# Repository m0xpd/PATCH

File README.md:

# PATCH
PATCH is a simple modular patchbay project for Eurorack.

PATCH started with an application to develop a simple interface to my [UMC1820 Audio Interface](https://www.behringer.com/product.html?modelCode=0805-AAN) and my [FX2000 Effects Processor](https://www.behringer.com/product.html?modelCode=P0A3P), both of which have rear-mounted audio I/O and require some input attentuators to allow them to work as I wish in my system. A patchbay is the perfect way to impose order on the tangle of wires, to avoid searching on the back of cases (especially if they're stacked or racked) and is also the logical place to implement attenuating pads, where required. 

The image below shows two PATCH patchbay modules (inside the yellow rounded rectangle) implementing the complete interface to the UMC1820 and FX2000

Note that the UMC1820 [does not need attenuators to handle modular signals directly](https://modwiggler.com/forum/viewtopic.php?p=2936306#p2936306). Indeed, it is specified to be capable of handling inputs up to +18dBu. However, this requires that the inputs are set to LINE (obviously), that the PADs are applied, and the GAIN controls are set way down near the bottom of their travel. I have been pleased to discover that in addition to service as front end of a DAW (or similar application), the UMC1820 also operates usefuly as a stand-alone mixer, with 8 channels going in and direct output to the system monitors. In this role, some external attenuation on the inputs is helpful, as it allows the GAIN controls to operate as Level 'faders' over a wider range, with more useful resolution. On the other hand, the FX2000 is specified only to handle inputs up to +4dBu and my modular was easily able to overload its inputs; an external attenuator is certainly required in this case. 

The basic PATCH configuration which services this motivating application, seen in the photos above, is realised by three components: a [front panel](https://github.com/m0xpd/PATCH/tree/main/Hardware/Front%20Panel#readme), a [socket board](https://github.com/m0xpd/PATCH/tree/main/Hardware/Socket%20Board#readme), and a [passive board](https://github.com/m0xpd/PATCH/tree/main/Hardware/Passive%20Board#readme). 

The passive board includes pi networks between the 3.5mm jack sockets at input and output of each channel and provides options to normal the 'tip switches' on the jacks to ground if the channel is configured as an input. This tip normalisation is achieved using 1206 surface mount (0 Ohm) resistors (as I figure not many people will bother to use them), whilst the rest of the board uses through-hole components. Partially populating the resistors of the pi network gives the option to set up a potential divider to drop the signal level in either direction, or to set a unity gain 'straight wire' connection. The system shown above has a 24dB pad on the top two channels and two send/return loops implemented on the next four sockets, with 12dB pads on the sends and straight-wire returns.

Populating the pads is up to you - I'm using a 15k / 1k potential divider for the -24dB and 3k3 / 1k1 potential divider for the -12dB. HOWEVER, you should remember that the device you're plugging into has finite (and possibly LOW) input impedance, which will sit in parallel with the botttom resistor of the potential divider, so either don't take the open-circuit calculations too seriously, or account for this loading in your design!

The Passive board, which makes up PATCH's standard patchbay configuration, houses a set of 3.5mm sockets which face to the rear, mirroring those on the front panel. Standard Eurorack patch leads (or other leads made up for custom applications, such as the 3.5 mm to 6.5mm right angle jacks I've made to hook up to the back of my FX2000) connect to these sockets, when the patchbay is used in the modular:

***

The minimum order quantity at [JLC](https://jlcpcb.com/) (typical of all pcb houses) for the front panel and socket board left me with some spare resources after I'd finished my interface to the Behringer "off-board" units, so I also develped a [passive multiple board](https://github.com/m0xpd/PATCH/tree/main/Hardware/Passive%20Multiple%20Board#readme), and a [buffered multiple board](https://github.com/m0xpd/PATCH/tree/main/Hardware/Buffered%20Multiple%20Board#readme) so as not to waste the relatively expensive Aluminium front panels. 

These multiples share the front panel and the socket board with the basic patchbay design, but use a different final board. 

The complete set of PATCH system panels are seen below.

Both the passive multiple and the buffered multiple are organised as two 1 in, 2 out sections, with the input to the second section normalled to the output of the first, such that the multiple can be operated as two 1 -> 2 units or one 1 -> 4 unit.

A PATCH buffered multiple is seen below:

All the system components are described in the [hardware folder](https://github.com/m0xpd/PATCH/tree/main/Hardware#readme), where schematics, PCB layouts and front panel designs are presented as [KiCad](https://www.kicad.org/) projects.

# PATCH Multicore

The PATCH system now (as at 5 June 2024) also has a multicore option, realised by a pair of boards. The multicore functionality was first suggested by "CoogLFish", within the "Issues" section of this repo and whose inspiration is acknowledged.

The boards are offered in two forms. First, the ["low budget"](https://github.com/m0xpd/PATCH/tree/main/Hardware/RJ45%20Board#readme) option uses a single UTP cable to join two modules to make a six channel multicore]. Second, the ["high end" alternative](https://github.com/m0xpd/PATCH/tree/main/Hardware/Twin%20RJ45%20Board#readme) uses two UTP cables to achieve the same goal with the possibility of slightly better crosstalk performance. This "Twin" system will also work with cables with shielded twisted pairs such as CAT8 and offer some performance advantages - but I have not yet formally tested this to determine how big the performance advantage (over either the single cable solution or UTP cables) really is. I use CAT6 cables over 1.5m and have not yet noticed issues.

# Other PATCH System Components

There may be still more additions to the PATCH system in future - I have a couple more ideas, but there are lots of other potential projects competing for attention, so watch this space, but don't hold your breath.

# License

PATCH is published under [CC BY-SA 4.0 license.](https://github.com/m0xpd/PATCH/blob/main/LICENSE.txt)

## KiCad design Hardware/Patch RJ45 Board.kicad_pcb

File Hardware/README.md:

This folder contains design files for components of the PATCH modular Eurorack patchbay system.

There are schematics, PCB layouts and a Front Panel design in [KiCad](https://www.kicad.org/) format.

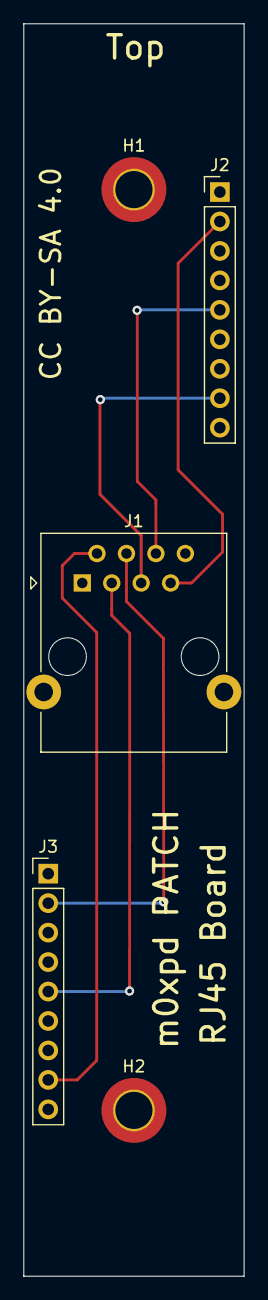
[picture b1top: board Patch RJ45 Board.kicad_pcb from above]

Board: 2 copper layers, 19.0 x 108.0 mm, 5 parts (0 on the bottom side), 7 nets.

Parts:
H1, H2: MountingHole_Pad; MountingHole_3.2mm_M3_DIN965_Pad_TopBottom
J1: RJ45_Shielded; RJ45_Ninigi_GE
J2, J3: Conn_01x09; PinHeader_1x09_P2.54mm_Vertical

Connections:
GND: H1.1, H2.1, J1.1, J1.8, J1.SH, J2.3, J2.6, J2.9, J3.3, J3.6, J3.9
unnamed: J1.7, J2.2
unnamed: J1.6, J2.5
unnamed: J1.5, J2.8
unnamed: J1.4, J3.2
unnamed: J1.3, J3.5
unnamed: J1.2, J3.8

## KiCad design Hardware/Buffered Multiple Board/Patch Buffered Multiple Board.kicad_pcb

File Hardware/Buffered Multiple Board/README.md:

# Buffered Multiple Board

This folder contains design files for the Buffered Multiple Board which (in conjuntion with the Socket Board and Front Panel) form an active, Buffered Multiple. 
The design files are presented as a [KiCad](https://www.kicad.org/) project.

The Buffered Multiple Board hosts two 9 * 1, 0.1 inch headers (to mount it on to the Socket Board),  a standard 2*5 Eurorack Power Header and filtering capacitors. 
It also hosts a quad op-amp (I used a TL084, but anything similar will work), the stages of which are used as voltage followers, and a few resistors to set the 
input and source impedance. 

The resulting buffered multiple is organised as two 1 in, 2 out sections, with the input to the second section normalled to the output of the first, 
such that the module can be operated as two 1 -> 2 multiples or one 1 -> 4 multiple.

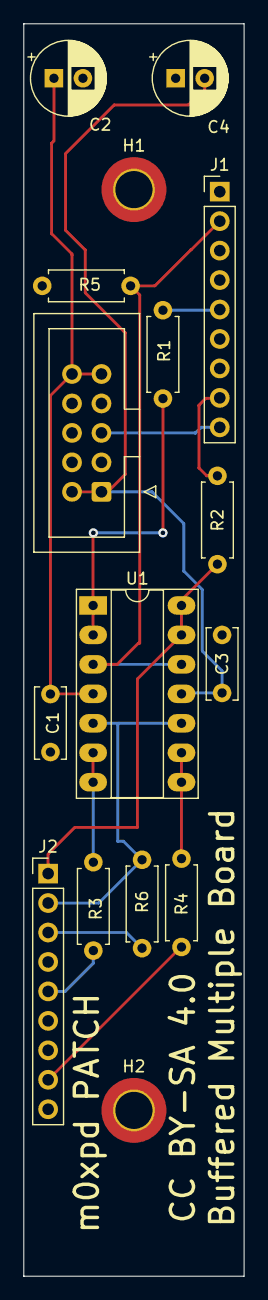
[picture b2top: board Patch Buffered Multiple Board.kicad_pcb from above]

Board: 2 copper layers, 19.0 x 108.0 mm, 16 parts (0 on the bottom side), 13 nets.

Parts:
C1, C3: 0.1u; C_Disc_D6.0mm_W2.5mm_P5.00mm
C2, C4: 22u; CP_Radial_D6.3mm_P2.50mm
H1, H2: MountingHole_Pad; MountingHole_3.2mm_M3_DIN965_Pad_TopBottom
J1, J2: Conn_01x09; PinHeader_1x09_P2.54mm_Vertical
R1, R2, R3, R4, R5, R6: R; R_Axial_DIN0207_L6.3mm_D2.5mm_P7.62mm_Horizontal
U1: TL084; DIP-14_W7.62mm_Socket_LongPads
X1: 2510-; IDC-Header_2x05_P2.54mm_Vertical

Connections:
+12V: C1.1, C2.1, U1.4 (V+), X1.9 (KL), X1.10 (KL)
-12V: C3.2, C4.2, U1.11 (V-), X1.1 (KL), X1.2 (KL)
GND: C1.2, C2.2, C3.1, C4.1, H1.1, H2.1, J1.3, J1.6, J1.9, J2.3, J2.6, J2.9, R5.1, R6.1, X1.3 (KL), X1.4 (KL), X1.5 (KL), X1.6 (KL), X1.7 (KL), X1.8 (KL)
IN1: J1.2, R5.2, U1.3 (+), U1.12 (+)
IN2: J2.2, R6.2, U1.5 (+), U1.10 (+)
unnamed: R1.1, U1.1, U1.2 (-)
unnamed: R3.1, U1.6 (-), U1.7
unnamed: R4.1, U1.8, U1.9 (-)
OUT1: J1.5, R1.2
OUT2: J1.8, R2.2
OUT2A: J2.1, R2.1, U1.13 (-), U1.14
OUT3: J2.5, R3.2
OUT4: J2.8, R4.2

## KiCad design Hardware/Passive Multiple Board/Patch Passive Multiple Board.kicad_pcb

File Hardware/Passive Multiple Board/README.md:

# Passive Multiple Board

This folder contains design files for the Passive Multiple Board which (in conjuntion with the Socket Board and Front Panel) form a Passive Multiple. 
The design files are presented as a [KiCad](https://www.kicad.org/) project.

The Passive Multiple Board is trivial, hosting only two 9*1 0.1 inch headers (to mount it on to the Socket Board) and containing tracks between the 
poles of these headers to make the electrical connections which define the circuit (see the Schematic).

The resulting passive multiple is organised as two 1 in, 2 out sections, with the input to the second section normalled to the output of the first, 
such that the module can be operated as two 1 -> 2 multiples or one 1 -> 4 multiple.

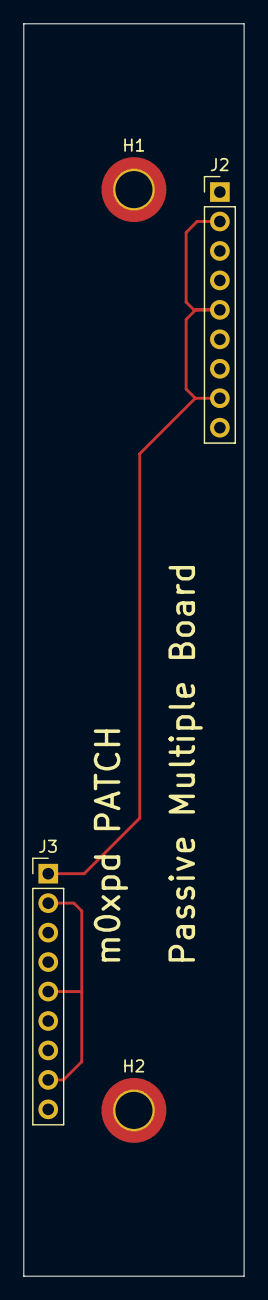
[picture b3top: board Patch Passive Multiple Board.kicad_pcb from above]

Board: 2 copper layers, 19.0 x 108.0 mm, 4 parts (0 on the bottom side), 3 nets.

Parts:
H1, H2: MountingHole_Pad; MountingHole_3.2mm_M3_DIN965_Pad_TopBottom
J2, J3: Conn_01x09; PinHeader_1x09_P2.54mm_Vertical

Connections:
GND: H1.1, H2.1, J2.3, J2.6, J2.9, J3.3, J3.6, J3.9
unnamed: J2.2, J2.5, J2.8, J3.1
unnamed: J3.2, J3.5, J3.8

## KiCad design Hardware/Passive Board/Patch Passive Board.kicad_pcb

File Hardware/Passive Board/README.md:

# Passive Board

This folder contains design files of the "Passive Board" which, in conjunction with the Front Panel and Socket Board, implements a simple six-channel patchbay. 
The design files are presented as a [KiCad](https://www.kicad.org/) project.

The Passive Board hosts six "[Thonkiconn](https://www.thonk.co.uk/shop/thonkiconn/)" 3.5mm sockets, which mirror those on the front panel and two 9*1 0.1 inch headers, which mount the Passive Board onto 
the Socket Board. 

A set of 12 positions for 1206 surface mount resistors on the bottom side of the board allow 0 Ohm links to be fitted, which normal the Tips of the sockets 
(on the Passive and Socket board) to ground, as required.

On the top side of the board, positions are provided for through hole resistors forming a "pi network" to be placed between each socket on the Socket Board and 
the corresponding socket on the Passive Board. This allows (by leaving one resistor unpopulated) for a potential divider to be fitted to attentuate the signal 
in either direction or (by fitting a 0 Ohm link - i.e. a wire  in the resistor position at the top of th 'pi' and leaving the other resistors unpopulated), making 
the channel a straight-wire connection.

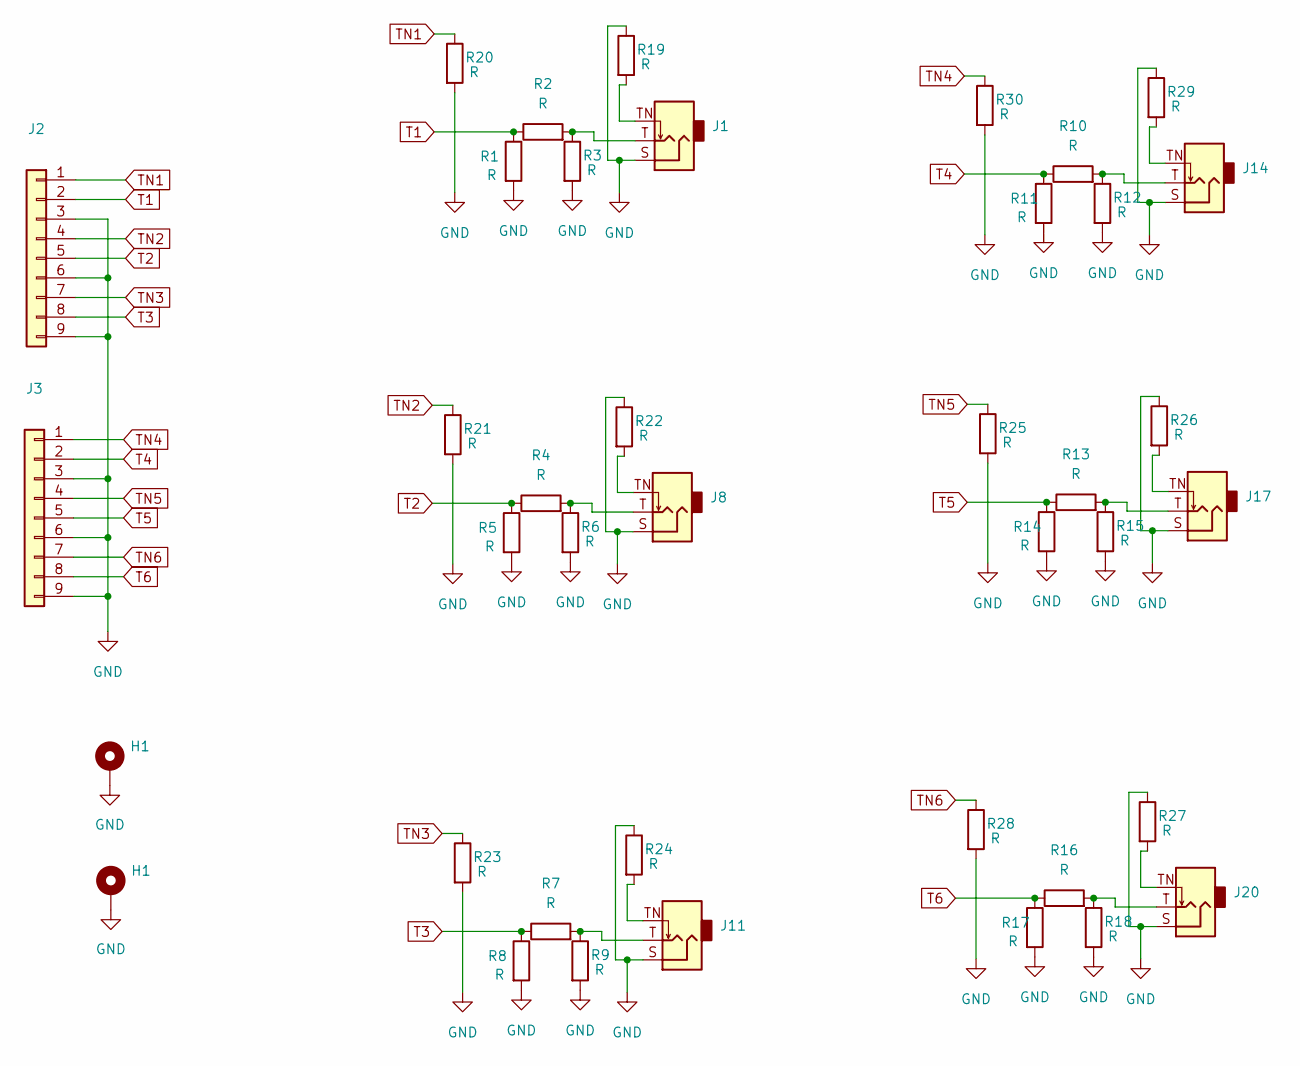
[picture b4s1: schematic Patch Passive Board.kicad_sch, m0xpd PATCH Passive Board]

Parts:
H1: MountingHole_Pad; MountingHole_3.2mm_M3_DIN965_Pad_TopBottom
J1, J8, J11, J14, J17, J20: AudioJack2_SwitchT; Jack_3.5mm_QingPu_WQP-PJ398SM_Vertical_CircularHoles
J2, J3: Conn_01x09; PinHeader_1x09_P2.54mm_Vertical
R1, R2, R3, R5, R8, R11, R14, R16, R17, R18: R; R_Axial_DIN0207_L6.3mm_D2.5mm_P2.54mm_Vertical
R4, R6, R7, R9, R10, R12, R13, R15: R; R_Axial_DIN0207_L6.3mm_D2.5mm_P7.62mm_Horizontal
R19, R20, R21, R22, R23, R24, R25, R26, R27, R28, R29, R30: R; R_1206_3216Metric_Pad1.30x1.75mm_HandSolder

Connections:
GND: H1.1, J1.S, J2.3, J2.6, J2.9, J3.3, J3.6, J3.9, J8.S, J11.S, J14.S, J17.S, J20.S, R1.2, R3.2, R5.2, R6.2, R8.2, R9.2, R11.2, R12.2, R14.2, R15.2, R17.2, R18.2, R19.1, R20.2, R21.2, R22.1, R23.2, R24.1, R25.2, R26.1, R27.1, R28.2, R29.1, R30.2; also elsewhere on the board
unnamed: J1.T, R2.2, R3.1
unnamed: J1.TN, R19.2
unnamed: J8.T, R4.2, R6.1
unnamed: J8.TN, R22.2
unnamed: J11.T, R7.2, R9.1
unnamed: J11.TN, R24.2
unnamed: J14.T, R10.2, R12.1
unnamed: J14.TN, R29.2
unnamed: J17.T, R13.2, R15.1
unnamed: J17.TN, R26.2
unnamed: J20.T, R16.2, R18.1
unnamed: J20.TN, R27.2
T1: J2.2, R1.1, R2.1
T2: J2.5, R4.1, R5.1
T3: J2.8, R7.1, R8.1
T4: J3.2, R10.1, R11.1
T5: J3.5, R13.1, R14.1
T6: J3.8, R16.1, R17.1
TN1: J2.1, R20.1
TN2: J2.4, R21.1
TN3: J2.7, R23.1
TN4: J3.1, R30.1
TN5: J3.4, R25.1
TN6: J3.7, R28.1

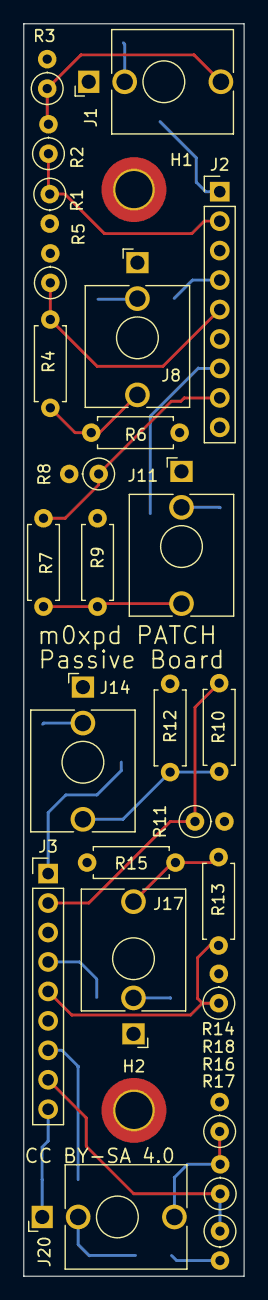
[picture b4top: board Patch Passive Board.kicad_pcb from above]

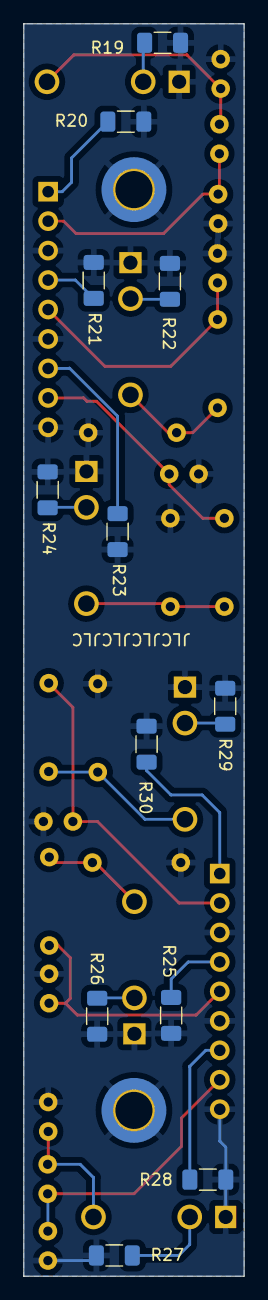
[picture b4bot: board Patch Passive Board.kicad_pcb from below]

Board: 2 copper layers, 19.0 x 108.0 mm, 40 parts (12 on the bottom side), 25 nets.

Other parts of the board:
H2: MountingHole_Pad; MountingHole_3.2mm_M3_DIN965_Pad_TopBottom

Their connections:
GND: H2.1; also elsewhere on the board

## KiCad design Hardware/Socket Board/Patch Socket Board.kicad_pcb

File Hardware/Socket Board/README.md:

# Socket Board

This folder contains design files for the "Socket Board", which is a common element of all PATCH applications. The files are in [KiCad](https://www.kicad.org/) format.

The Socket Board carries six "[Thonkiconn](https://www.thonk.co.uk/shop/thonkiconn/)" 3.5mm sockets (by which it mounts to the Front Panel) and two 9*1 0.1 inch female header sockets (by which other PATCH boards plug onto the back of the socket board. I find it convenient to cut these 9-way receptacles down from 40-way units, which I keep in stock.

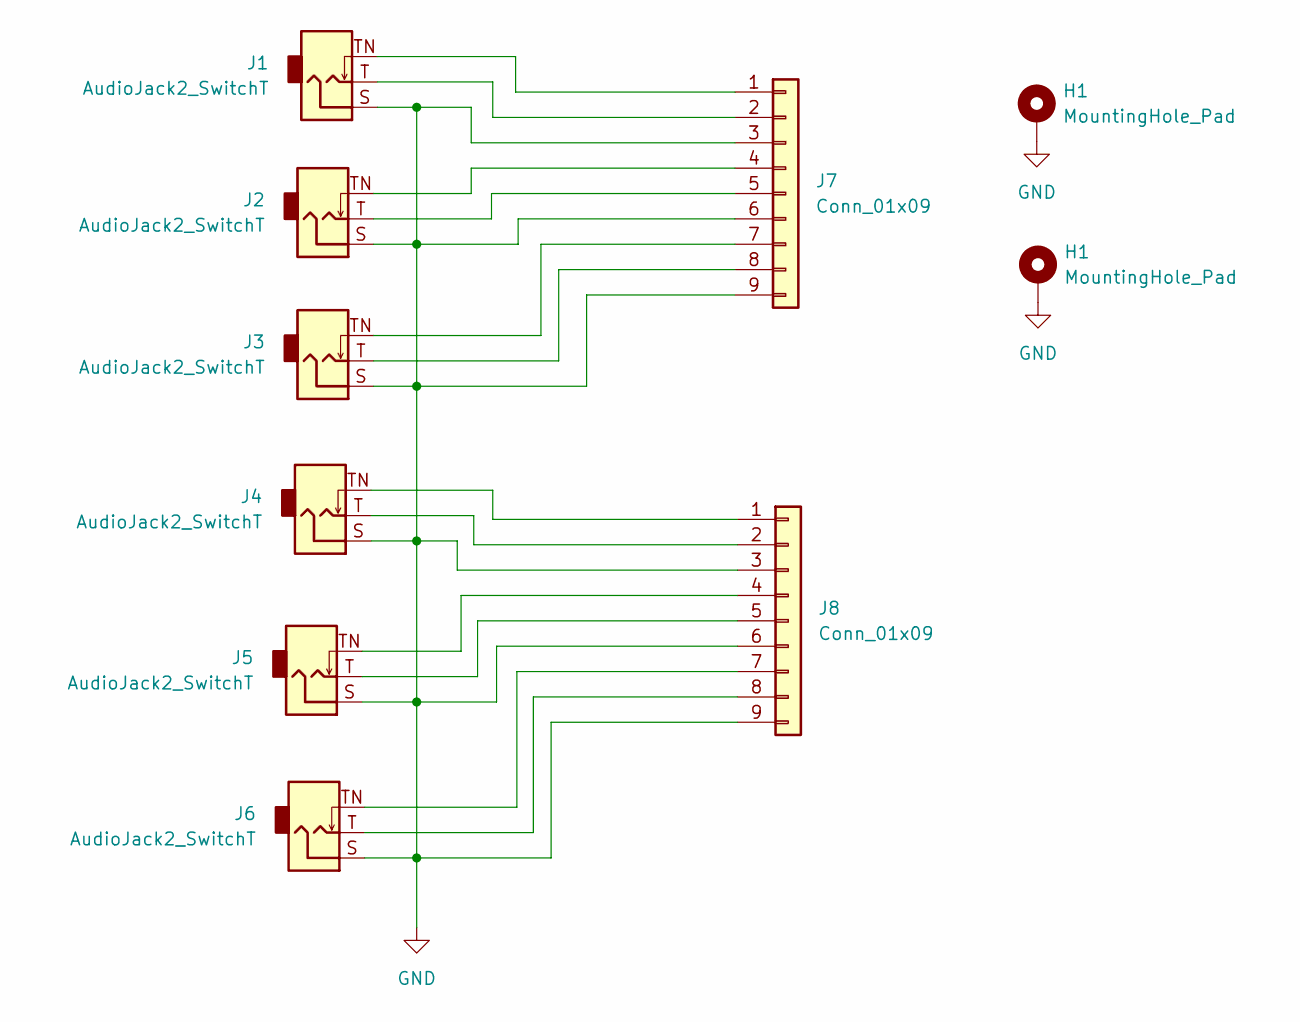
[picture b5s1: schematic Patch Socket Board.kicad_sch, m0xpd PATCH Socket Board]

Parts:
H1: MountingHole_Pad; MountingHole_3.2mm_M3_DIN965_Pad_TopBottom
J1, J2, J3, J4, J5, J6: AudioJack2_SwitchT; Jack_3.5mm_QingPu_WQP-PJ398SM_Vertical_CircularHoles
J7, J8: Conn_01x09; PinHeader_1x09_P2.54mm_Vertical

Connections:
GND: H1.1, J1.S, J2.S, J3.S, J4.S, J5.S, J6.S, J7.3, J7.6, J7.9, J8.3, J8.6, J8.9; also elsewhere on the board
unnamed: J1.TN, J7.1
unnamed: J1.T, J7.2
unnamed: J2.TN, J7.4
unnamed: J2.T, J7.5
unnamed: J3.TN, J7.7
unnamed: J3.T, J7.8
unnamed: J4.TN, J8.1
unnamed: J4.T, J8.2
unnamed: J5.TN, J8.4
unnamed: J5.T, J8.5
unnamed: J6.TN, J8.7
unnamed: J6.T, J8.8

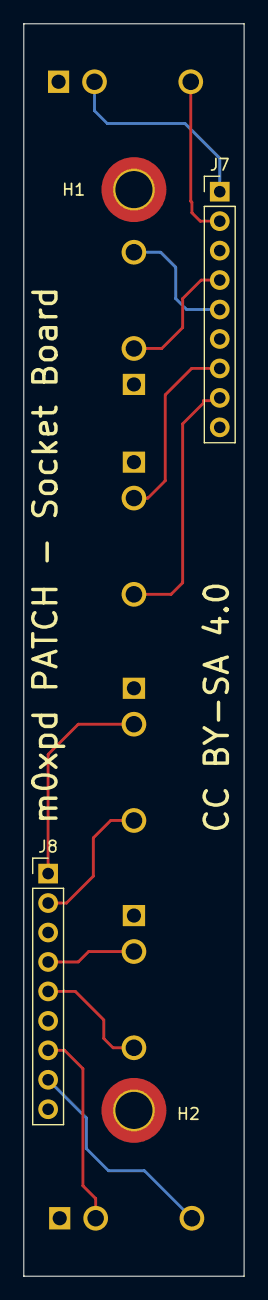
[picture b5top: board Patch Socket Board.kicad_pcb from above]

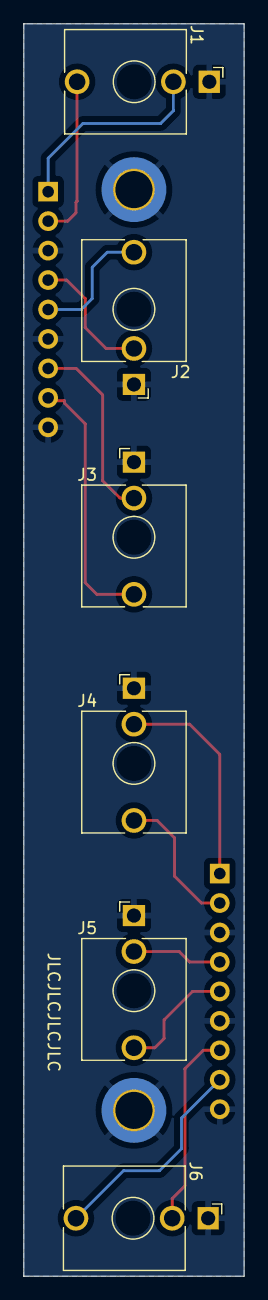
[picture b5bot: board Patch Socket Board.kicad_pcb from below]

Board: 2 copper layers, 19.0 x 108.0 mm, 10 parts (6 on the bottom side), 13 nets.

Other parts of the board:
H2: MountingHole_Pad; MountingHole_3.2mm_M3_DIN965_Pad_TopBottom

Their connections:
GND: H2.1; also elsewhere on the board

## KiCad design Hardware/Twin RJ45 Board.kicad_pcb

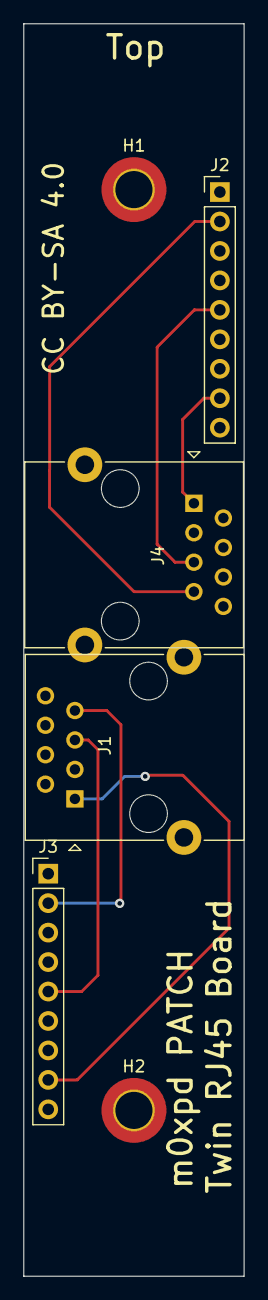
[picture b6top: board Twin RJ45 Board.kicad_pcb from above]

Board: 2 copper layers, 19.0 x 108.0 mm, 6 parts (0 on the bottom side), 7 nets.

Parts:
H1, H2: MountingHole_Pad; MountingHole_3.2mm_M3_DIN965_Pad_TopBottom
J1, J4: RJ45_Shielded; RJ45_Ninigi_GE
J2, J3: Conn_01x09; PinHeader_1x09_P2.54mm_Vertical

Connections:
GND: H1.1, H2.1, J1.2, J1.3, J1.4, J1.6, J1.8, J1.SH, J2.3, J2.6, J2.9, J3.3, J3.6, J3.9, J4.2, J4.3, J4.4, J4.6, J4.8, J4.SH
unnamed: J2.2, J4.7
unnamed: J2.5, J4.5
unnamed: J2.8, J4.1
unnamed: J1.7, J3.2
unnamed: J1.5, J3.5
unnamed: J1.1, J3.8

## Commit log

2024-03-23 Rename Patch Perspective.jpg to Hardware/Patch Perspective.jpg
2024-03-23 Rename Hardware/Patch Perspective.jpg to Hardware/Images/Patch Perspective.jpg
2024-03-23 Rename Patch Front Panel.kicad_pcb to Hardware/Patch Front Panel.kicad_pcb
2024-03-23 Rename Patch Front Panel.kicad_pro to Hardware/Patch Front Panel.kicad_pro
2024-03-23 Rename Patch Front Panel.kicad_sch to Hardware/Patch Front Panel.kicad_sch
2024-03-23 Rename Hardware/Patch Front Panel.kicad_pcb to Hardware/Front Panel/Patch Front Panel.kicad_pcb
2024-03-23 Rename Hardware/Patch Front Panel.kicad_pro to Hardware/Front Panel/Patch Front Panel.kicad_pro
2024-03-23 Rename Hardware/Patch Front Panel.kicad_sch to Hardware/Front Panel/Patch Front Panel.kicad_sch
2024-03-23 Rename Hardware/Patch Socket Board.kicad_pro to Hardware/Socket Board/Patch Socket Board.kicad_pro
2024-03-23 Rename Hardware/Patch Passive Board.kicad_pro to Hardware/Passive Board/Patch Passive Board.kicad_pro
2024-03-23 Rename Hardware/Patch Passive Multiple Board.kicad_pro to Hardware/Passive Multiple Board/Patch Passive Multiple Board.kicad_pro
2024-03-23 Rename Hardware/Patch Buffered Multiple Board.kicad_pcb to Hardware/Buffered Multiple Board/Patch Buffered Multiple Board.kicad_pcb
2024-06-05 Rename Hardware/Patch RJ45 Board.jpg to Hardware/Images/Patch RJ45 Board.jpg
2024-06-05 Rename Hardware/Patch Twin RJ45 Board.jpg to Hardware/Images/Patch Twin RJ45 Board.jpg
2024-06-05 Rename Hardware/RJ45 Multicore.jpg to Hardware/Images/RJ45 Multicore.jpg
2024-06-05 Rename Hardware/Twin RJ45 Module Rear.jpg to Hardware/Images/Twin RJ45 Module Rear.jpg
2024-06-05 Rename Hardware/Patch RJ45 Board.kicad_pcb to Hardware/RJ45 Board/Patch RJ45 Board.kicad_pcb
2024-06-05 Rename Hardware/Patch RJ45 Board.kicad_pro to Hardware/RJ45 Board/Patch RJ45 Board.kicad_pro
2024-06-05 Rename Hardware/Patch RJ45 Board.kicad_sch to Hardware/RJ45 Board/Patch RJ45 Board.kicad_sch
2024-06-05 Rename Hardware/Twin RJ45 Board.kicad_pcb to Hardware/Twin RJ45 Board/Twin RJ45 Board.kicad_pcb
2024-06-05 Rename Hardware/Twin RJ45 Board.kicad_pro to Hardware/Twin RJ 45 Board/Twin RJ45 Board.kicad_pro
2024-06-05 Rename Hardware/Twin RJ45 Board.kicad_sch to Hardware/Twin RJ45 Board/Twin RJ45 Board.kicad_sch
2024-06-05 Rename Hardware/Twin RJ45 Board.kicad_pro to Hardware/Twin RJ45 Board/Twin RJ45 Board.kicad_pro
